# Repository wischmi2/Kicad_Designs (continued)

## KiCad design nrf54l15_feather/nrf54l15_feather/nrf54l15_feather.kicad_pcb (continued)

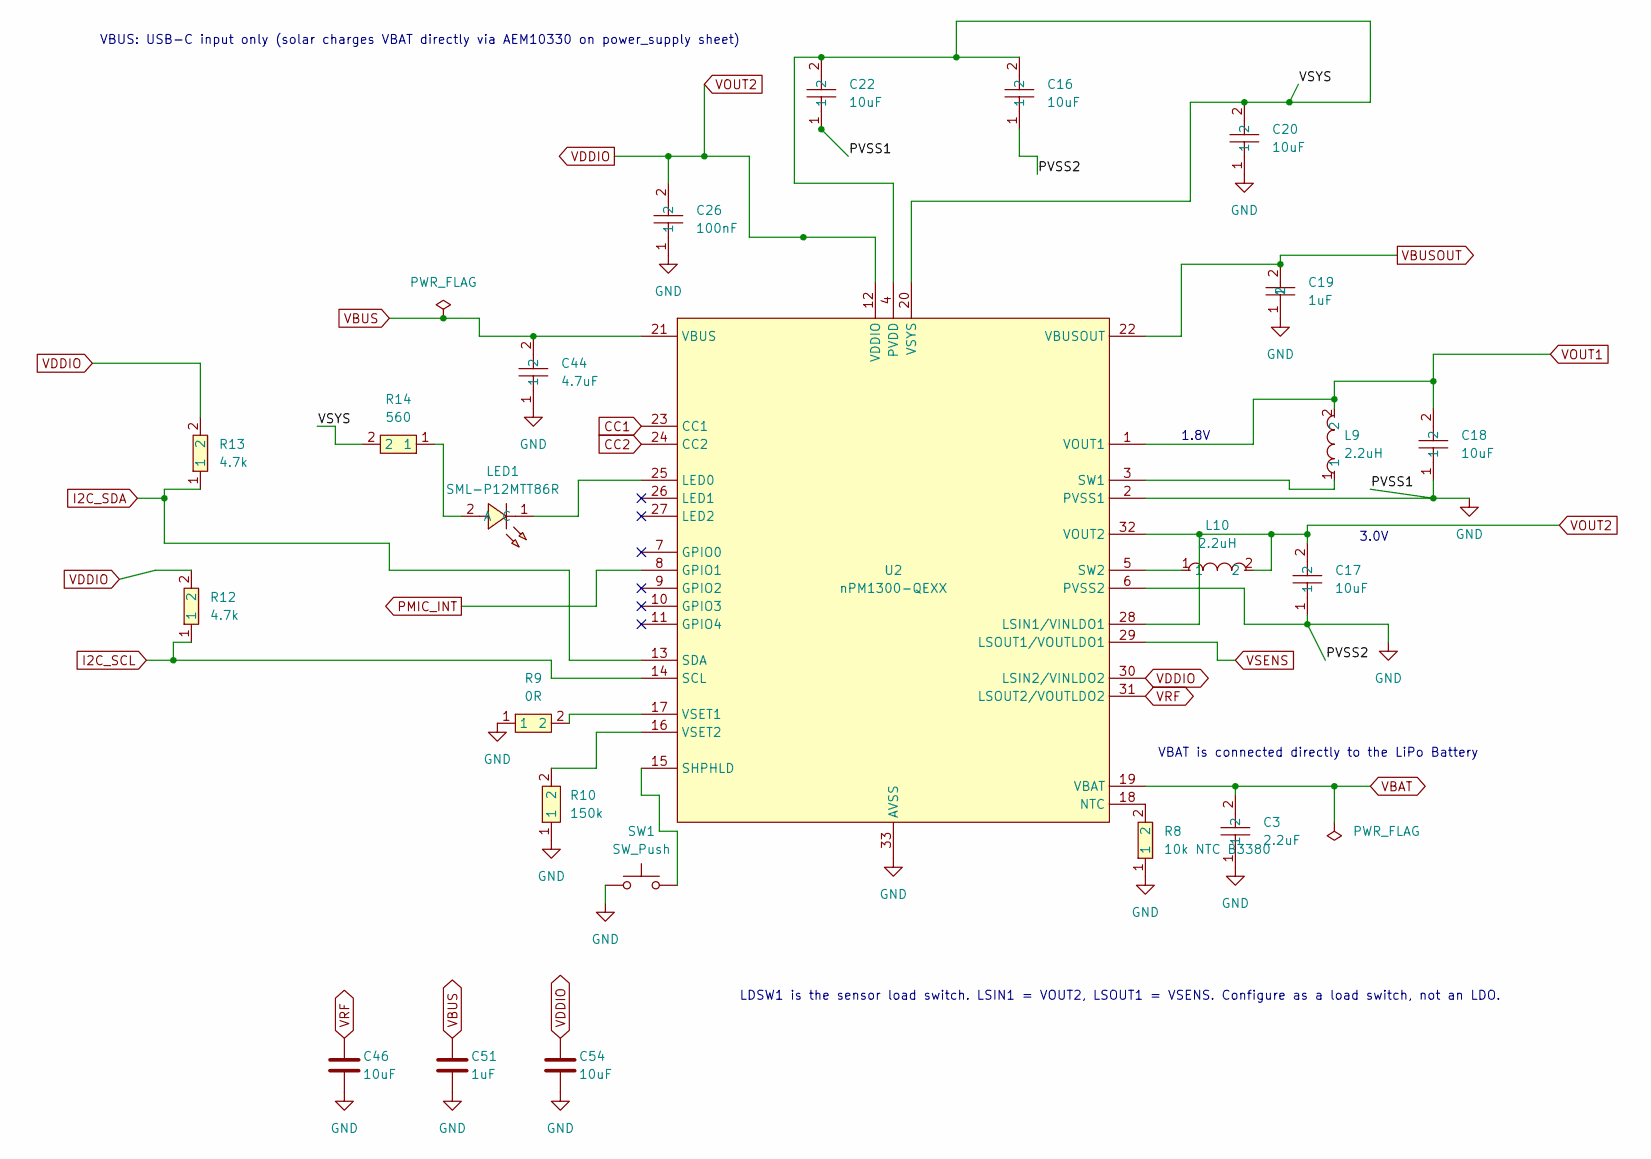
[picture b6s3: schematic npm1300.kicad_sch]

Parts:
C3: 2.2uF; C0603; MPN CL10A225KB8NNNC; LCSC Part C913904
C16: 10uF; C0603; MPN CC0603MRX5R8BB106; LCSC Part C596327
C17, C18, C20, C22: 10uF; C0805; MPN CL21A106KAYNNNE; LCSC Part C15850
C19: 1uF; C0402; MPN CL05A105KO5NNNC; LCSC Part C29266
C26: 100nF; C0603; MPN CC0603KRX7R9BB104; LCSC Part C14663
C44: 4.7uF; C0805; MPN CL21A475KAQNNNE; LCSC Part C1779
C46: 10uF; C_0603_1608Metric; MPN CL10A106KP8NNNC; LCSC C19702
C51: 1uF; C_0402_1005Metric; MPN CL05A105KA5NQNC; LCSC C52923
C54: 10uF; C_0402_1005Metric; MPN CL05A106MQ5NUNC; LCSC C15525
L9, L10: 2.2uH; L0603; MPN LSCNB1608HKT2R2MD; LCSC Part C6079477
LED1: SML-P12MTT86R; LED-SMD_L1.0-W0.6-RD_SML-P12YTT86RR; MPN SML-P12MTT86R; LCSC Part C510304
R8: 10k NTC B3380; R0402; MPN NCP15XH103F03RC; LCSC Part C77131
R9: 0R; R0603; MPN 0603WAF0000T5E; LCSC Part C21189
R10: 150k; R0603; MPN FRC0603F1503TS; LCSC Part C2906993
R12, R13: 4.7k; R0402; MPN RC0402FR-074K7L; LCSC Part C105871
R14: 560; R0402; MPN FRC0402F5600TS; LCSC Part C2909370
SW1: SW_Push; SW_SPST_B3U-1000P; MPN B3U-1000P
U2: nPM1300-QEXX; QFN-32-1EP_5x5mm_P0.5mm_EP3.6x3.6mm_ThermalVias; MPN nPM1300-QEAA-R7

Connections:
/npm1300/VSYS: C16.2, C20.2, C22.2, R14.2, U2.4 (PVDD), U2.20 (VSYS)
CC1: U2.23 (CC1); also elsewhere on the board
CC2: U2.24 (CC2); also elsewhere on the board
GND: C3.1, C16.1, C17.1, C18.1, C19.1, C20.1, C22.1, C26.1, C44.1, C46.2, C51.2, C54.2, R8.1, R9.1, R10.1, SW1.1, U2.2 (PVSS1), U2.6 (PVSS2), U2.33 (AVSS); also elsewhere on the board
I2C_SCL: R12.1, U2.14 (SCL); also elsewhere on the board
I2C_SDA: R13.1, U2.13 (SDA); also elsewhere on the board
unnamed: LED1.2 (A), R14.1
unnamed: LED1.1 (C), U2.25 (LED0)
unnamed: R8.2, U2.18 (NTC)
unnamed: SW1.2, U2.15 (SHPHLD)
unnamed: L9.1, U2.3 (SW1)
unnamed: L10.1, U2.5 (SW2)
unnamed: R9.2, U2.17 (VSET1)
unnamed: R10.2, U2.16 (VSET2)
PMIC_INT: U2.8 (GPIO1); also elsewhere on the board
VBAT: C3.2, U2.19 (VBAT); also elsewhere on the board
VBUS: C44.2, C51.1, U2.21 (VBUS); also elsewhere on the board
VBUSOUT: C19.2, U2.22 (VBUSOUT)
VDDIO: C17.2, C26.2, C54.1, L10.2, R12.2, R13.2, U2.12 (VDDIO), U2.28 (LSIN1/VINLDO1), U2.30 (LSIN2/VINLDO2), U2.32 (VOUT2); also elsewhere on the board
VOUT1: C18.2, L9.2, U2.1 (VOUT1)
VRF: C46.1, U2.31 (LSOUT2/VOUTLDO2); also elsewhere on the board
VSENS: U2.29 (LSOUT1/VOUTLDO1); also elsewhere on the board

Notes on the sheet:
1.8V
VBAT is connected directly to the LiPo Battery
LDSW1 is the sensor load switch. LSIN1 = VOUT2, LSOUT1 = VSENS. Configure as a load switch, not an LDO.
VBUS: USB-C input only (solar charges VBAT directly via AEM10330 on power_supply sheet)
3.0V

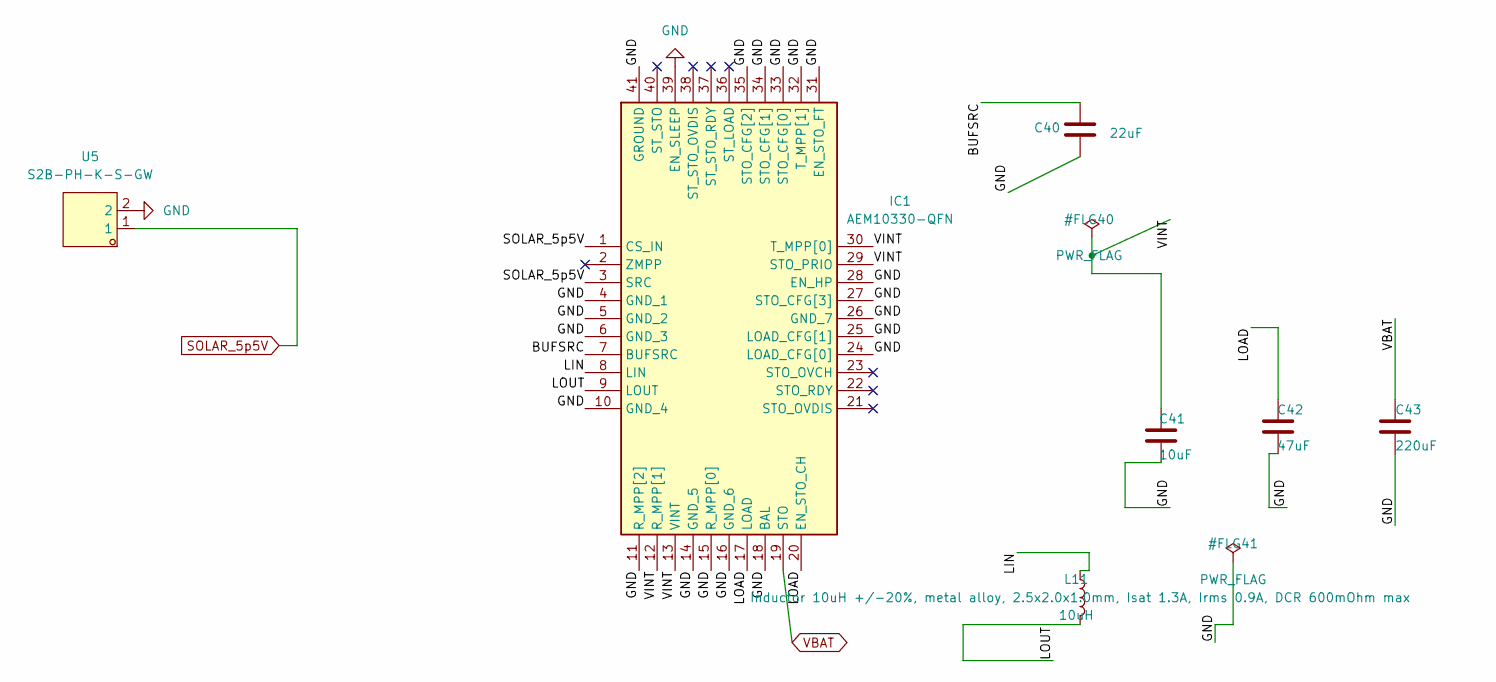
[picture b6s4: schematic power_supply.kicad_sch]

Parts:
C40: 22uF; C_0603_1608Metric; MPN GRM188R61A226ME15D
C41: 10uF; C_0402_1005Metric; MPN GRM155R60J106ME15
C42: 47uF; C_0603_1608Metric; MPN GRM188R60J476ME15D
C43: 220uF; C_1206_3216Metric; MPN MSASJ31LBB5227MTCA01
IC1: AEM10330-QFN; QFN40P500X500X85-41N-D; Mouser Part Number 120-AEM10330-QFN
L11: 10uH; L_Sunlord_SWPA252010S; MPN DFE252010F-100M=P2; LCSC Part C701155
U5: S2B-PH-K-S-GW; CONN-TH_S2B-PH-K-S-GW; MPN S2B-PH-K-S-GW; LCSC Part C157932

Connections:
/Solar/BUFSRC: C40.1, IC1.7 (BUFSRC)
/Solar/LIN: IC1.8 (LIN), L11.1
/Solar/LOAD: C42.1, IC1.17 (LOAD), IC1.20 (EN_STO_CH)
/Solar/LOUT: IC1.9 (LOUT), L11.2
/Solar/VINT: C41.1, IC1.12 (R_MPP[1]), IC1.13 (VINT), IC1.29 (STO_PRIO), IC1.30 (T_MPP[0])
GND: C40.2, C41.2, C42.2, C43.2, IC1.4 (GND_1), IC1.5 (GND_2), IC1.6 (GND_3), IC1.10 (GND_4), IC1.11 (R_MPP[2]), IC1.14 (GND_5), IC1.15 (R_MPP[0]), IC1.16 (GND_6), IC1.18 (BAL), IC1.24 (LOAD_CFG[0]), IC1.25 (LOAD_CFG[1]), IC1.26 (GND_7), IC1.27 (STO_CFG[3]), IC1.28 (EN_HP), IC1.31 (EN_STO_FT), IC1.32 (T_MPP[1]), IC1.33 (STO_CFG[0]), IC1.34 (STO_CFG[1]), IC1.35 (STO_CFG[2]), IC1.39 (EN_SLEEP), IC1.41 (GROUND), U5.2; also elsewhere on the board
SOLAR_5p5V: IC1.1 (CS_IN), IC1.3 (SRC), U5.1
VBAT: C43.1, IC1.19 (STO); also elsewhere on the board

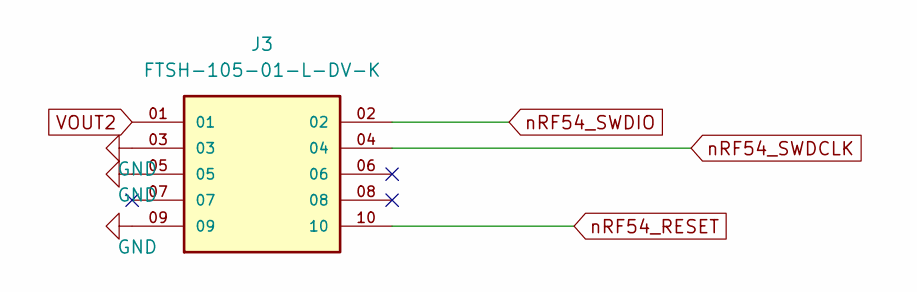
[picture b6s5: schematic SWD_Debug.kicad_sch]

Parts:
J3: FTSH-105-01-L-DV-K; SAMTEC_FTSH-105-01-L-DV-K; MPN FTSH-105-01-L-DV-K-TR

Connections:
GND: J3.03, J3.05, J3.09; also elsewhere on the board
VDDIO: J3.01; also elsewhere on the board
nRF54_RESET: J3.10; also elsewhere on the board
nRF54_SWDCLK: J3.04; also elsewhere on the board
nRF54_SWDIO: J3.02; also elsewhere on the board

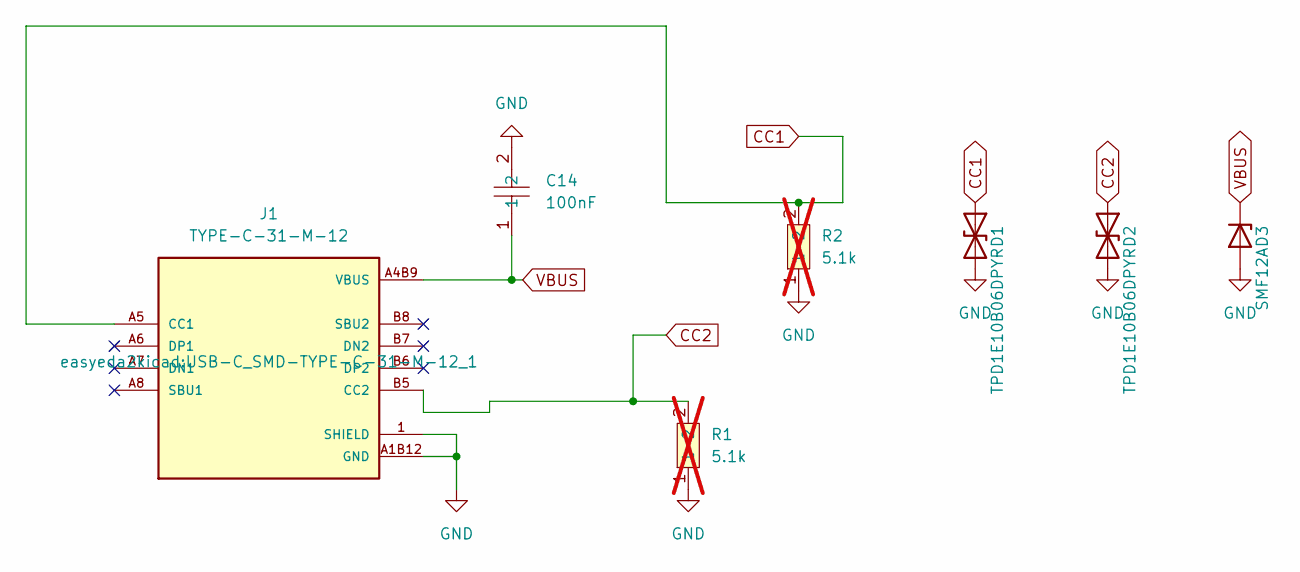
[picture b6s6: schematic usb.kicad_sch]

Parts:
C14: 100nF; C0603; MPN CC0603KRX7R9BB104; LCSC Part C14663
D1, D2: TPD1E10B06DPYR; Texas_DPY0002A_0.6x1mm_P0.65mm; MPN TPD1E10B06DPYR; LCSC C48260
D3: SMF12A; D_SOD-123F; MPN SMF12A; LCSC C207255
J1: TYPE-C-31-M-12; USB-C_SMD-TYPE-C-31-M-12_1; MPN TYPE-C-31-M-12; LCSC Part C165948
R1, R2: 5.1k; R0402; MPN RCA025K1FLF; LCSC Part C22369457; not fitted

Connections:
CC1: D1.1 (A1), J1.A5 (CC1), R2.2; also elsewhere on the board
CC2: D2.1 (A1), J1.B5 (CC2), R1.2; also elsewhere on the board
GND: C14.2, D1.2 (A2), D2.2 (A2), D3.2 (A), J1.1 (SHIELD), J1.2 (SHIELD), J1.3 (SHIELD), J1.4 (SHIELD), J1.A1B12 (GND), J1.B1A12 (GND), R1.1, R2.1; also elsewhere on the board
VBUS: C14.1, D3.1 (K), J1.A4B9 (VBUS), J1.B4A9 (VBUS); also elsewhere on the board

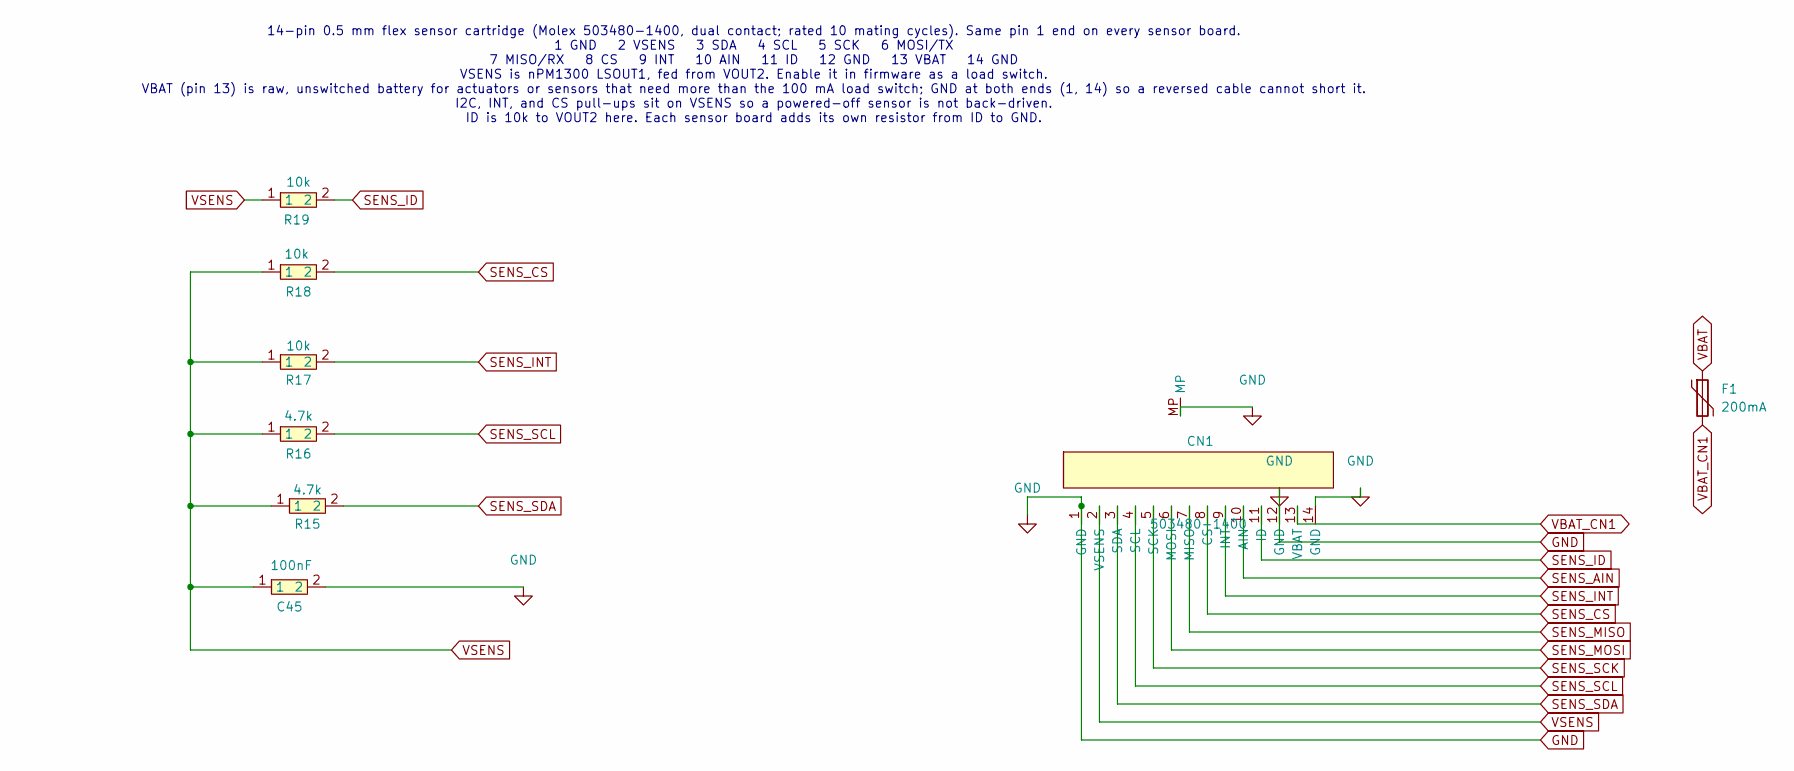
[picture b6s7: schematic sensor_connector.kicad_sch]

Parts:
C45: 100nF; C0402; MPN CL05B104KO5NNNC
CN1: 503480-1400; Molex_503480-1400_1x14-1MP_P0.50mm_Horizontal; MPN 503480-1400
F1: 200mA; Fuse_0603_1608Metric; MPN MF-FSMF020X-2; LCSC C210356
R15, R16: 4.7k; R0402; MPN RC0402FR-074K7L
R17, R18, R19: 10k; R0402; MPN RT0402BRD0710KL; LCSC Part C190095

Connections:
GND: C45.2, CN1.1 (GND), CN1.12 (GND), CN1.14 (GND), CN1.MP; also elsewhere on the board
SENS_AIN: CN1.10 (AIN); also elsewhere on the board
SENS_CS: CN1.8 (CS), R18.2; also elsewhere on the board
SENS_ID: CN1.11 (ID), R19.2; also elsewhere on the board
SENS_INT: CN1.9 (INT), R17.2; also elsewhere on the board
SENS_MISO: CN1.7 (MISO); also elsewhere on the board
SENS_MOSI: CN1.6 (MOSI); also elsewhere on the board
SENS_SCK: CN1.5 (SCK); also elsewhere on the board
SENS_SCL: CN1.4 (SCL), R16.2; also elsewhere on the board
SENS_SDA: CN1.3 (SDA), R15.2; also elsewhere on the board
VBAT: F1.1; also elsewhere on the board
VBAT_CN1: CN1.13 (VBAT), F1.2
VSENS: C45.1, CN1.2 (VSENS), R15.1, R16.1, R17.1, R18.1, R19.1; also elsewhere on the board

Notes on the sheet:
14-pin 0.5 mm flex sensor cartridge (Molex 503480-1400, dual contact; rated 10 mating cycles). Same pin 1 end on every sensor board. 1 GND 2 VSENS 3 SDA 4 SCL 5 SCK 6 MOSI/TX 7 MISO/RX 8 CS 9 INT 10 AIN 11 ID 12 GND 13 VBAT 14 GND VSENS is nPM1300 LSOUT1, fed from VOUT2. Enable it in firmware as a 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

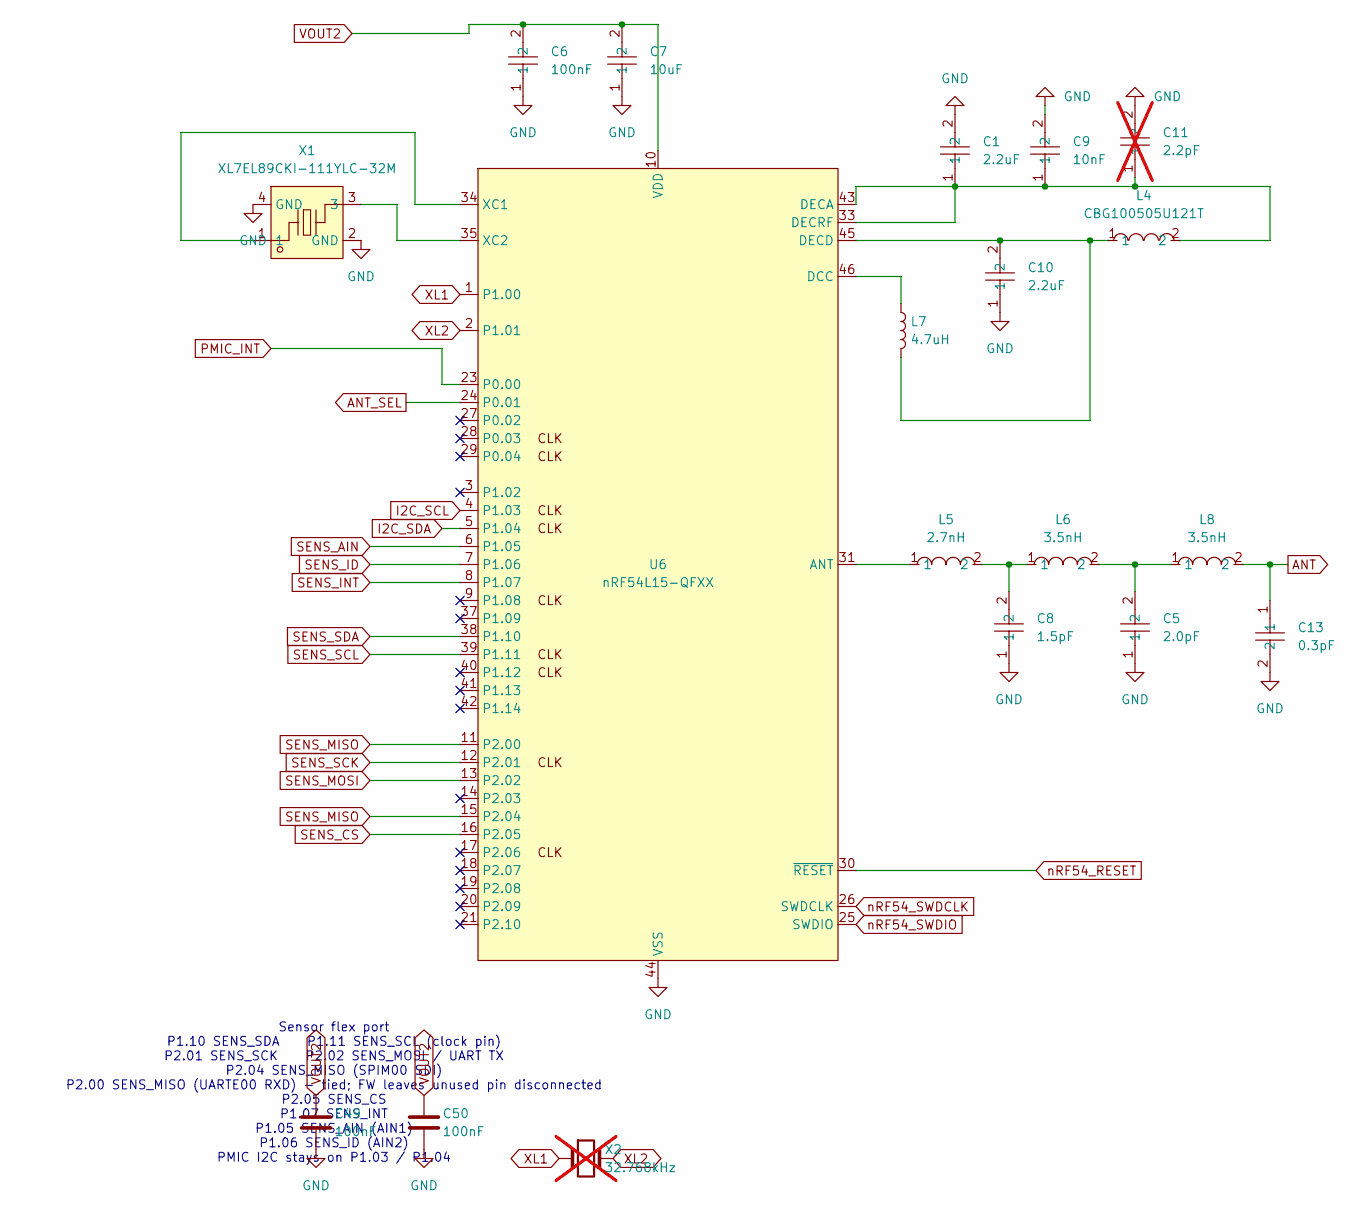
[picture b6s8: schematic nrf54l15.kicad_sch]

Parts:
C1, C10: 2.2uF; C0201; MPN GRM033R61A225KE47D; LCSC Part C335106
C5: 2.0pF; C0201; MPN GJM0335C1E2R0WB01D; LCSC Part C668326
C6: 100nF; C0603; MPN CC0603KRX7R9BB104; LCSC Part C14663
C7: 10uF; C0805; MPN CL21A106KAYNNNE; LCSC Part C15850
C8: 1.5pF; C0201; MPN GJM0335C1E1R5WB01D; LCSC Part C435397
C9: 10nF; C0402; MPN GCM155R71H103KA55D; LCSC Part C91601
C11: 2.2pF; C0201; MPN GJM0335C1E2R2WB01D; LCSC Part C710732; not fitted
C13: 0.3pF; C0201; MPN GJM0335C1ER30WB01D; LCSC Part C161289
C49, C50: 100nF; C_0201_0603Metric; MPN CL03A104KQ3NNNC; LCSC C160831
L4: CBG100505U121T; L0402; MPN CBG100505U121T; LCSC Part C92616
L5: 2.7nH; L0201; MPN LQP03HQ2N7B02D; LCSC Part C7216765
L6, L8: 3.5nH; L0201; MPN LQP03HQ3N5B02D; LCSC Part C3911055
L7: 4.7uH; L0603; MPN LQM18PH4R7MFRL; LCSC Number C1858257
U6: nRF54L15-QFXX; QFN-48-1EP_6x6mm_P0.4mm_EP4.6x4.6mm_ThermalVias; MPN nRF54L15-QFAA-R
X1: XL7EL89CKI-111YLC-32M; CRYSTAL-SMD_4P-L2.0-W1.6-BL; MPN XL7EL89CKI-111YLC-32M; LCSC Part C2965582
X2: 32.768kHz; Crystal_SMD_2012-2Pin_2.0x1.2mm; MPN X1A0000610008; LCSC C96341; not fitted

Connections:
ANT: C13.1, L8.2; also elsewhere on the board
ANT_SEL: U6.24 (P0.01); also elsewhere on the board
GND: C1.2, C5.1, C6.1, C7.1, C8.1, C9.2, C10.1, C11.2, C13.2, C49.2, C50.2, U6.32 (VSS_PA), U6.44 (VSS), U6.49 (VSS), X1.2 (GND), X1.4 (GND); also elsewhere on the board
I2C_SCL: U6.4 (P1.03); also elsewhere on the board
I2C_SDA: U6.5 (P1.04); also elsewhere on the board
unnamed: C5.2, L6.2, L8.1
unnamed: C8.2, L5.2, L6.1
unnamed: L5.1, U6.31 (ANT)
unnamed: L7.1, U6.46 (DCC)
unnamed: C1.1, C9.1, C11.1, L4.2, U6.33 (DECRF), U6.43 (DECA)
unnamed: C10.2, L4.1, L7.2, U6.45 (DECD)
unnamed: U6.34 (XC1), X1.1
unnamed: U6.35 (XC2), X1.3
PMIC_INT: U6.23 (P0.00); also elsewhere on the board
SENS_AIN: U6.6 (P1.05); also elsewhere on the board
SENS_CS: U6.16 (P2.05); also elsewhere on the board
SENS_ID: U6.7 (P1.06); also elsewhere on the board
SENS_INT: U6.8 (P1.07); also elsewhere on the board
SENS_MISO: U6.11 (P2.00), U6.15 (P2.04); also elsewhere on the board
SENS_MOSI: U6.13 (P2.02); also elsewhere on the board
SENS_SCK: U6.12 (P2.01); also elsewhere on the board
SENS_SCL: U6.39 (P1.11); also elsewhere on the board
SENS_SDA: U6.38 (P1.10); also elsewhere on the board
VDDIO: C6.2, C7.2, C49.1, C50.1, U6.10 (VDD), U6.22 (VDD), U6.36 (VDD), U6.47 (VDD), U6.48 (VDD); also elsewhere on the board
XL1: U6.1 (P1.00), X2.1
XL2: U6.2 (P1.01), X2.2
nRF54_RESET: U6.30 (~RESET); also elsewhere on the board
nRF54_SWDCLK: U6.26 (SWDCLK); also elsewhere on the board
nRF54_SWDIO: U6.25 (SWDIO); also elsewhere on the board

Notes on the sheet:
Sensor flex port P1.10 SENS_SDA P1.11 SENS_SCL (clock pin) P2.01 SENS_SCK P2.02 SENS_MOSI / UART TX P2.04 SENS_MISO (SPIM00 SDI) P2.00 SENS_MISO (UARTE00 RXD) - tied; FW leaves unused pin disconnected P2.05 SENS_CS P1.07 SENS_INT P1.05 SENS_AIN (AIN1) P1.06 SENS_ID (AIN2) PMIC I2C stays on P1.03 / 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

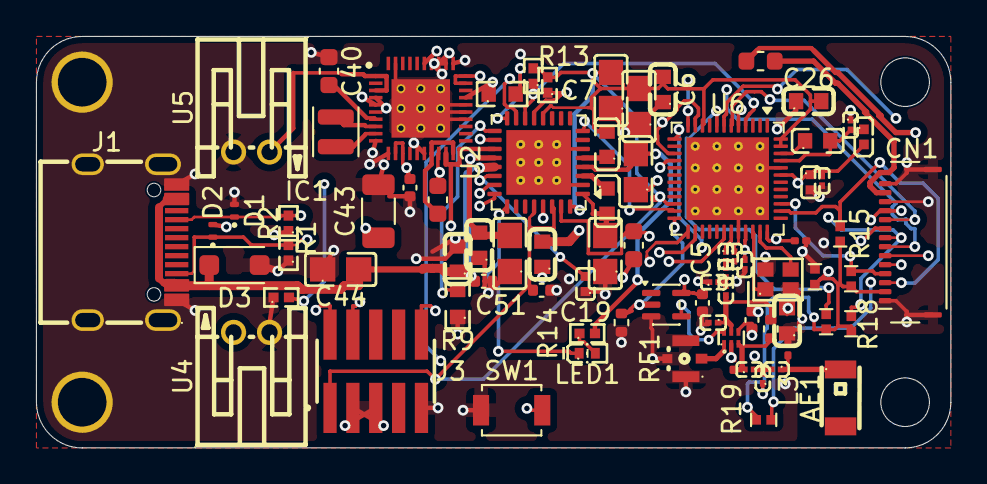
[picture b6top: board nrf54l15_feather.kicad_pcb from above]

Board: 4 copper layers, 50.8 x 22.9 mm, 83 parts (0 on the bottom side), 56 nets.

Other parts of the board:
H1, H2: M2.5 plated; MountingHole_2.5mm_Pad
H3, H4: M2.5 NPTH (nylon); MountingHole_2.5mm

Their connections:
GND: H1.1, H2.1; also elsewhere on the board

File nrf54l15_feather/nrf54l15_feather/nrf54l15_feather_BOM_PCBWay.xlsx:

|  |  | nrf54l15_feather — PCB Assembly BOM
Item # | *Designator | *Qty | Manufacturer | *Mfg Part # | Description / Value | *Package/Footprint | Type | Your Instructions / Notes
1 | C45 | 1 | Samsung Electro-Mechanics | CL05B104KO5NNNC | CAP CER 100nF 16V X7R ±10% 0402 | 0402 | SMD | LCSC: C1525
2 | C6,C14,C15,C26 | 4 | YAGEO | CC0603KRX7R9BB104 | CAP CER 100nF 50V X7R ±10% 0603 | 0603 | SMD | LCSC: C14663
3 | C9 | 1 | Murata | GCM155R71H103KA55D | CAP CER 10nF 50V X7R ±10% 0402 | 0402 | SMD | LCSC: C91601
4 | C4,C19 | 2 | Samsung Electro-Mechanics | CL05A105KO5NNNC | CAP CER 1uF 16V X5R ±10% 0402 | 0402 | SMD | LCSC: C29266
5 | C1,C10 | 2 | Murata | GRM033R61A225KE47D | CAP CER 2.2uF 10V X5R ±10% 0201 | 0201 | SMD | LCSC: C335106
6 | C3 | 1 | Samsung Electro-Mechanics | CL10A225KB8NNNC | CAP CER 2.2uF 50V X5R ±10% 0603 | 0603 | SMD | LCSC: C913904
7 | C41 | 1 | Murata | GRM155R60J106ME15 | CAP CER 10uF 6.3V X5R ±20% 0402 | 0402 | SMD | No LCSC stock for ME15; GRM155R60J106ME44D (LCSC: C76991) acceptable alternate
8 | C16 | 1 | YAGEO | CC0603MRX5R8BB106 | CAP CER 10uF 25V X5R ±20% 0603 | 0603 | SMD | LCSC: C596327
9 | C7,C17,C18,C20,C22,C44 | 6 | Samsung Electro-Mechanics | CL21A106KAYNNNE | CAP CER 10uF 25V X5R ±10% 0805 | 0805 | SMD | LCSC: C15850
10 | C40 | 1 | Murata | GRM188R61A226ME15D | CAP CER 22uF 10V X5R ±20% 0603 | 0603 | SMD | LCSC: C84419
11 | C42 | 1 | Murata | GRM188R60J476ME15D | CAP CER 47uF 6.3V X5R ±20% 0603 | 0603 | SMD | LCSC: C140782
12 | C43 | 1 | Taiyo Yuden | MSASJ31LBB5227MTCA01 | CAP CER 220uF 1206 | 1206 | SMD | No LCSC part #; please quote sourcing
13 | C13 | 1 | Murata | GJM0335C1ER30WB01D | CAP CER 0.3pF 25V C0G ±0.05pF 0201 (RF) | 0201 | SMD | LCSC: C161289; RF match — do not substitute
14 | C12 | 1 | Murata | GJM0335C1E1R0WB01D | CAP CER 1.0pF 25V C0G ±0.05pF 0201 (RF) | 0201 | SMD | LCSC: C185624; RF match — do not substitute
15 | C8 | 1 | Murata | GJM0335C1E1R5WB01D | CAP CER 1.5pF 25V C0G ±0.05pF 0201 (RF) | 0201 | SMD | LCSC: C435397; RF match — do not substitute
16 | C5 | 1 | Murata | GJM0335C1E2R0WB01D | CAP CER 2.0pF 25V C0G ±0.05pF 0201 (RF) | 0201 | SMD | LCSC: C668326; RF match — do not substitute
17 | C11 | 1 | Murata | GJM0335C1E2R2WB01D | CAP CER 2.2pF 25V C0G ±0.05pF 0201 (RF) | 0201 | SMD | LCSC: C710732; RF match — do not substitute
18 | R14 | 1 | FOJAN | FRC0402F5600TS | RES 560 OHM 1% 0402 | 0402 | SMD | LCSC: C2909370
19 | R12,R13,R15,R16 | 4 | YAGEO | RC0402FR-074K7L | RES 4.7K OHM 1% 1/16W 0402 | 0402 | SMD | LCSC: C105871
20 | R1,R2 | 2 | HKR | RCA025K1FLF | RES 5.1K OHM 1% 0402 | 0402 | SMD | LCSC: C22369457
21 | R8,R17,R18,R19 | 4 | YAGEO | RT0402BRD0710KL | RES 10K OHM 0.1% 0402 | 0402 | SMD | LCSC: C190095
22 | R9 | 1 | FOJAN | FRC0603F4702TS | RES 47K OHM 1% 0603 | 0603 | SMD | LCSC: C2907042
23 | R10 | 1 | FOJAN | FRC0603F1503TS | RES 150K OHM 1% 0603 | 0603 | SMD | LCSC: C2906993
24 | L2,L5 | 2 | Murata | LQP03HQ2N7B02D | INDUCTOR RF 2.7nH ±0.1nH 0201 | 0201 | SMD | LCSC: C7216765; RF match — do not substitute
25 | L6,L8 | 2 | Murata | LQP03HQ3N5B02D | INDUCTOR RF 3.5nH ±0.1nH 0201 | 0201 | SMD | LCSC: C3911055; RF match — do not substitute
26 | L3 | 1 | Murata | LQP03HQ3N9B02D | INDUCTOR RF 3.9nH ±0.1nH 0201 | 0201 | SMD | LCSC: C337939; RF match — do not substitute
27 | L4 | 1 | FH (Fenghua) | CBG100505U121T | FERRITE BEAD 120 OHM @100MHz 0402 | 0402 | SMD | LCSC: C92616
28 | L9,L10 | 2 | Taiyo Yuden | LSCNB1608HKT2R2MD | INDUCTOR PWR 2.2uH ±20% 0603 | 0603 | SMD | LCSC: C6079477
29 | L7 | 1 | Murata | LQM18PH4R7MFRL | INDUCTOR PWR 4.7uH ±20% 0603 | 0603 | SMD | LCSC: C1858257
30 | L11 | 1 | Murata | DFE252010F-100M=P2 | INDUCTOR PWR 10uH ±20% 2.5x2.0mm | SMD 2.5x2.0mm | SMD | LCSC: C701155
31 | LED1 | 1 | ROHM | SML-P12MTT86R | LED RED 1006 (0402) | 1006 (0402) | SMD | LCSC: C510304; polarity per silkscreen
32 | U6 | 1 | Nordic Semiconductor | nRF54L15-QFAA-R | IC SoC BLE 2.4GHz ARM Cortex-M33 QFN-48 6x6mm | QFN-48 6x6mm P0.4mm | SMD | LCSC: C42458750; pin 1 per silkscreen
33 | U2 | 1 | Nordic Semiconductor | nPM1300-QEAA-R7 | IC PMIC CHARGER + 2x BUCK + 2x LDO/LOAD SW QFN-32 5x5mm | QFN-32 5x5mm P0.5mm | SMD | QFN-32 package required (do NOT substitute CSP variant); please quote sourcing.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
34 | IC1 | 1 | e-peas | AEM10330-QFN | IC ENERGY HARVESTING PMIC (solar) QFN-40 5x5mm | QFN-40 5x5mm P0.4mm | SMD | No LCSC part #; Mouser: 120-AEM10330-QFN; please quote sourcing. Pin 1 per silk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
35 | R11 | 1 | FM (Fuman) | FM8625H | IC RF SWITCH SPDT DFN-6 1.1x0.7mm | DFN-6 1.1x0.7mm P0.4mm | SMD | LCSC: C2857391; this is an IC (not a resistor) despite R designator. Pin 1 per 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
36 | X1 | 1 | YXC | XL7EL89CKI-111YLC-32M | CRYSTAL 32MHz SMD 2.0x1.6mm 4-pad | SMD 2.0x1.6mm | SMD | LCSC: C2965582
37 | AE1 | 1 | Johanson Technology | 2450AT18A100E | ANTENNA CHIP 2.45GHz 3.2x1.6mm | SMD 3.2x1.6mm | SMD | LCSC: C89334; orientation per silkscreen
38 | RF1 | 1 | ECT | ECT818000500 | CONN RF COAX RCPT SMD | SMD | SMD | LCSC: C437254
39 | J1 | 1 | Korean Hroparts Elec (HRO) | TYPE-C-31-M-12 | CONN USB TYPE-C RCPT 16P SMD R/A | SMD | SMD | LCSC: C165948
40 | CN1 | 1 | Molex | 503480-1400 | CONN FFC/FPC 14POS 0.5mm R/A SMD | 1x14 P0.50mm SMD | SMD | No LCSC part #; please quote sourcing. Pin 1 per silkscreen
41 | J3 | 1 | Samtec | FTSH-105-01-L-DV-K-TR | CONN HDR 2x5 1.27mm SMD VERT (SWD) | 2x5 P1.27mm SMD | SMD | LCSC: C448647; BOTTOM SIDE. Pin 1 per silkscreen
42 | SW1 | 1 | Omron | B3U-1000P | SWITCH TACTILE SPST-NO SMD 3.0x2.5mm | SMD 3.0x2.5mm | SMD | No LCSC part # assigned; please quote sourcing
43 | U4,U5 | 2 | JST | S2B-PH-K-S-GW | CONN HDR PH 2POS 2.0mm R/A THT | 1x2 P2.00mm R/A THT | thru-hole | LCSC: C157932; BOTTOM SIDE
Need a quick and accurante quote? Need an efficient production? Please read SMT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
Click for Instructions on How to Create a BOM

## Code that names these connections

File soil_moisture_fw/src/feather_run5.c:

#include <zephyr/kernel.h>
#include <zephyr/device.h>
#include <zephyr/drivers/adc.h>
#include <zephyr/drivers/gpio.h>
#include <zephyr/drivers/regulator.h>
#include <zephyr/logging/log.h>

#include "feather_run5.h"

LOG_MODULE_REGISTER(feather, LOG_LEVEL_INF);

/* nPM1300 LDO1 node = LDSW1 = VSENS, LDO2 node = LDSW2 = VRF (see the board dts). */
static const struct device *const vsens = DEVICE_DT_GET(DT_NODELABEL(npm1300_ek_ldo1));
static const struct device *const vrf = DEVICE_DT_GET(DT_NODELABEL(npm1300_ek_ldo2));
static const struct gpio_dt_spec ant_sel = GPIO_DT_SPEC_GET(DT_ALIAS(ant_sel), gpios);
static const struct adc_dt_spec sens_id = ADC_DT_SPEC_GET_BY_IDX(DT_PATH(zephyr_user), 0);

/* R19 pull-up on SENS_ID to VSENS, nominal VSENS (VDDIO via LSIN1, load switch mode). */
#define SENS_ID_PULLUP_OHM 10000
#define VSENS_NOMINAL_MV   3000
/* Settling time after VSENS on before sampling (load switch ramp + C45 + sensor board). */
#define VSENS_SETTLE_MS    20
/* Above this fraction of VSENS the pin is treated as open (no sensor board). */
#define SENS_ID_OPEN_MV    2900

int feather_vrf_check(void)
{
	int32_t uv = 0;
	int err;

	if (!device_is_ready(vrf)) {
		LOG_ERR("VRF regulator not ready");
		return -ENODEV;
	}

	if (!regulator_is_enabled(vrf)) {
		LOG_ERR("VRF (LDSW2) is not enabled");
		return -EIO;
	}

	err = regulator_get_voltage(vrf, &uv);
	if (err) {
		LOG_ERR("VRF get voltage failed (%d)", err);
		return err;
	}

	LOG_INF("VRF on, %d mV", uv / 1000);

	if (uv != 2500000) {
		LOG_WRN("VRF is not 2.5 V");
		return -EINVAL;
	}

	/* ANT_SEL was driven low by the gpio-hog before VRF came up. Report the level. */
	if (gpio_is_ready_dt(&ant_sel)) {
		LOG_INF("ANT_SEL (P0.01) reads %d (0 = chip antenna)",
			gpio_pin_get_raw(ant_sel.port, ant_sel.pin));
	}

	return 0;
}

int feather_read_sens_id(int32_t *pin_mv, uint32_t *rid_ohm)
{
	int16_t raw = 0;
	int32_t mv;
	int err;
	struct adc_sequence seq = {
		.buffer = &raw,
		.buffer_size = sizeof(raw),
	};

	if (!device_is_ready(vsens) || !adc_is_ready_dt(&sens_id)) {
		return -ENODEV;
	}

	err = adc_channel_setup_dt(&sens_id);
	if (err) {
		return err;
	}

	err = adc_sequence_init_dt(&sens_id, &seq);
	if (err) {
		return err;
	}

	err = regulator_enable(vsens);
	if (err) {
		LOG_ERR("VSENS enable failed (%d)", err);
		return err;
	}

	k_msleep(VSENS_SETTLE_MS);

	err = adc_read_dt(&sens_id, &seq);

	/* Always switch VSENS off again; SENS_ID is only valid while VSENS is on. */
	(void)regulator_disable(vsens);

	if (err) {
		LOG_ERR("SENS_ID ADC read failed (%d)", err);
		return err;
	}

	mv = raw;
	err = adc_raw_to_millivolts_dt(&sens_id, &mv);
	if (err) {
		return err;
	}

	*pin_mv = mv;
	if (mv >= SENS_ID_OPEN_MV) {
		*rid_ohm = 0;
	} else if (mv <= 0) {
		*rid_ohm = 0; /* shorted: also not a valid ID */
	} else {
		*rid_ohm = (uint32_t)(((int64_t)SENS_ID_PULLUP_OHM * mv) /
				      (VSENS_NOMINAL_MV - mv));
	}

	return 0;
}

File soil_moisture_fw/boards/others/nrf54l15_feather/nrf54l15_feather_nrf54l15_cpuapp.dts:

/dts-v1/;

#include <nordic/nrf54l15_cpuapp.dtsi>
#include <dt-bindings/regulator/npm13xx.h>
#include <zephyr/dt-bindings/adc/adc.h>
#include <zephyr/dt-bindings/adc/nrf-saadc.h>
#include "nrf54l15_feather-pinctrl.dtsi"

/*
 * nRF54L15 Feather main board (nrf54l15_feather, run 5 schematic, 2026-10-28).
 * Derived from the soil_moisture board file; see ../../../README.md
 * "Feather run 5 firmware" for the sources of every setting below.
 *
 * Netlist facts used (kicad-cli export of nrf54l15_feather.kicad_sch, 2026-10-28):
 *   I2C_SCL  U6.4  P1.03     I2C_SDA  U6.5  P1.04
 *   PMIC_INT U6.23 P0.00 <- U2.8 GPIO1
 *   ANT_SEL  U6.24 P0.01 -> U7.2 (SN74AUP1G34, VCC = VRF) -> ANT_VCTL -> R11.6 (FM8625H VCTL)
 *   SENS_ID  U6.7  P1.06 (SAADC AIN2), R19 10k pull-up to VSENS
 *   VSENS    U2.29 LSOUT1/VOUTLDO1 (nPM1300 LDSW1), input LSIN1 = VDDIO
 *   VRF      U2.31 LSOUT2/VOUTLDO2 (nPM1300 LDSW2), input LSIN2 = VDDIO
 *   BUCK1    U2.1 VOUT1 (VSET1 grounded through R9 0R, so OFF), only L9/C18 on it
 */

/ {
	model = "nRF54L15 Feather";
	compatible = "others,nrf54l15-feather-nrf54l15-cpuapp";

	chosen {
		zephyr,code-partition = &slot0_partition;
		zephyr,sram = &cpuapp_sram;
		zephyr,flash-controller = &rram_controller;
		zephyr,flash = &cpuapp_rram;
		zephyr,console = &rtt0;
		zephyr,shell-uart = &rtt0;
		zephyr,bt-mon-uart = &rtt0;
		zephyr,bt-c2h-uart = &rtt0;
		zephyr,ieee802154 = &ieee802154;
	};

	aliases {
		ant-sel = &ant_sel;
		watchdog0 = &wdt31;
	};

	antennas {
		compatible = "gpio-leds";

		/* Active high = level on P0.01. Low = ANT-RF1 = chip antenna AE1 (FM8625H truth
		 * table: VCTL 0 -> RF1, 1 -> RF2 = U.FL). U7 is non-inverting.
		 */
		ant_sel: ant_sel {
			gpios = <&gpio0 1 GPIO_ACTIVE_HIGH>;
			label = "RF switch ANT_SEL (U7 -> FM8625H VCTL)";
		};
	};

	zephyr,user {
		/* SENS_ID, read only while VSENS is on */
		io-channels = <&adc 0>;
	};

	rtt0: rtt_uart0 {
		compatible = "segger,rtt-uart";
		status = "okay";
	};
};

#include <vendor/nordic/nrf54l15_cpuapp_partition.dtsi>

&cpuapp_sram {
	status = "okay";
};

/* X2 (32.768 kHz) is DNP on run 5. These nodes are kept from the soil_moisture file;
 * the LFCLK source is chosen in prj.conf / Kconfig, not here.
 */
&lfxo {
	load-capacitors = "internal";
	load-capacitance-femtofarad = <17000>;
};

&hfxo {
	load-capacitors = "internal";
	load-capacitance-femtofarad = <15000>;
};

&regulators {
	status = "okay";
};

&vregmain {
	status = "okay";
	regulator-initial-mode = <NRF5X_REG_MODE_DCDC>;
};

&grtc {
	owned-channels = <0 1 2 3 4 5 6 7 8 9 10 11>;
	child-owned-channels = <3 4 7 8 9 10 11>;
	status = "okay";
};

&gpio0 {
	status = "okay";

	/*
	 * Drive ANT_SEL (P0.01) low (chip antenna) as early as the GPIO hog init allows
	 * (POST_KERNEL, priority 41), well before the nPM1300 regulator driver (priority
	 * 85/86) turns VRF on. U7's input must not float while VRF is up (SCES603K).
	 */
	ant_sel_hog: ant-sel-hog {
		gpio-hog;
		gpios = <1 GPIO_ACTIVE_HIGH>;
		output-low;
	};
};

&gpio1 {
	status = "okay";
};

&gpio2 {
	status = "okay";
};

&gpiote20 {
	status = "okay";
};

&gpiote30 {
	status = "okay";
};

&radio {
	status = "okay";
};

&ieee802154 {
	status = "okay";
};

&temp {
	status = "okay";
};

&clock {
	status = "okay";
};

/* SENS_ID on P1.06 = SAADC AIN2. R19 = 10k to VSENS (3.0 V); the sensor board puts its
 * ID resistor to GND, so the pin sits at VSENS * Rid / (Rid + 10k), 0..VSENS (open).
 * Gain 1/4 on the internal reference gives a 3.6 V full scale. 40 us acquisition
 * covers up to about 10k source impedance.
 */
&adc {
	status = "okay";
	#address-cells = <1>;
	#size-cells = <0>;

	channel@0 {
		reg = <0>;
		zephyr,gain = "ADC_GAIN_1_4";
		zephyr,reference = "ADC_REF_INTERNAL";
		zephyr,acquisition-time = <ADC_ACQ_TIME(ADC_ACQ_TIME_MICROSECONDS, 40)>;
		zephyr,input-positive = <NRF_SAADC_AIN2>; /* P1.06 SENS_ID */
		zephyr,resolution = <12>;
		zephyr,oversampling = <4>;
	};
};

&uart20 {
	status = "disabled";
};

&uart30 {
	status = "disabled";
};

&i2c21 {
	compatible = "nordic,nrf-twim";
	status = "okay";
	clock-frequency = <I2C_BITRATE_STANDARD>;
	pinctrl-0 = <&i2c21_default>;
	pinctrl-1 = <&i2c21_sleep>;
	pinctrl-names = "default", "sleep";

	npm1300_ek_pmic: pmic@6b {
		compatible = "nordic,npm1300";
		reg = <0x6b>;
		host-int-gpios = <&gpio0 0 GPIO_ACTIVE_HIGH>;
		pmic-int-pin = <1>;

		npm1300_ek_gpio: gpio-controller {
			compatible = "nordic,npm1300-gpio";
			gpio-controller;
			#gpio-cells = <2>;
			ngpios = <5>;
		};

		npm1300_ek_regulators: regulators {
			compatible = "nordic,npm1300-regulator";

			/*
			 * BUCK1 is deliberately NOT declared. VSET1 is grounded through R9 (0R),
			 * which the nPM1300 PS defines as "0 V (OFF)", and L9/C18 are the only
			 * load. With no BUCK1 child node the regulator driver creates no device
			 * for it and nothing in this firmware can write BUCK1ENASET or its
			 * voltage registers. Do not add a BUCK1 node.
			 */

			/* BUCK2 = VDDIO, 3.0 V set by the VSET2 strap (R10 150k). No init-microvolt,
			 * so the driver does not write a software voltage; it only reads the output
			 * voltage and snaps it into the window if the strap is wrong.
			 */
			npm1300_ek_buck2: BUCK2 {
				regulator-min-microvolt = <2900000>;
				regulator-max-microvolt = <3100000>;
				regulator-always-on;
			};

			/*
			 * LDSW1 = VSENS, 3.0 V from VDDIO via LSIN1 (U2.29 to CN1.2, C45, R15-R19).
			 * Left in its reset state (off, load-switch mode). The application turns it
			 * on only around SENS_ID reads or when a sensor board needs power.
			 */
			npm1300_ek_ldo1: LDO1 {
				regulator-min-microvolt = <1000000>;
				regulator-max-microvolt = <3300000>;
			};

			/*
			 * LDSW2 = VRF, LDO mode, 2.5 V, for R11 (FM8625H VDD 1.65-3.3 V) and U7
			 * (SN74AUP1G34 VCC). Input LSIN2 = VDDIO 3.0 V (VINLDO 2.6 V to VSYS).
			 * The driver (regulator_common_init) applies, in this order: initial mode
			 * (LDOSEL = LDO), init voltage (VOUTSEL 2.5 V), then enables the output
			 * (always-on) and waits startup-delay-us. Always on from boot on purpose:
			 * the radio can be used at any time and the load is about 50-90 uA.
			 * startup-delay-us 1000 is a conservative software wait for the output
			 * to rise and the switch to settle (the switch needs about 10 us after
			 * power-up); the real ramp time is a bench item.
			 */
			npm1300_ek_ldo2: LDO2 {
				regulator-min-microvolt = <2500000>;
				regulator-max-microvolt = <2500000>;
				regulator-init-microvolt = <2500000>;
				regulator-initial-mode = <NPM13XX_LDSW_MODE_LDO>;
				regulator-always-on;
				startup-delay-us = <1000>;
			};
		};

		npm1300_ek_charger: charger {
			compatible = "nordic,npm1300-charger";
			term-microvolt = <4150000>;
			term-warm-microvolt = <4000000>;
			/* Run 5: charge current capped at 300 mA or less (0.25 mm VBAT/VBUS tracks).
			 * 150 mA is kept from the soil_moisture file; raise to at most 300000.
			 */
			current-microamp = <150000>;
			dischg-limit-microamp = <1000000>;
			/* VBUS input limit 300 mA (binding range 100 mA to 1500 mA, 100 mA steps).
			 * Leaves about 150 mA for the system next to 150 mA charge.
			 */
			vbus-limit-microamp = <300000>;
			/* R8 = Murata NCP15XH103F03RC, 10k, B25/50 = 3380 K */
			thermistor-ohms = <10000>;
			thermistor-beta = <3380>;
			charging-enable;
		};

		npm1300_ek_leds: leds {
			compatible = "nordic,npm1300-led";
			nordic,led0-mode = "error";
			nordic,led1-mode = "charging";
			nordic,led2-mode = "host";
		};
	};
};
